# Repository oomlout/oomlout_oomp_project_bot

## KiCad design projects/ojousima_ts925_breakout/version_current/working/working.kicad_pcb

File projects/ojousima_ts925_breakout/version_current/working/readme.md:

# OOMP Project  
## TS925-breakout  by ojousima  
  
oomp key: oomp_projects_flat_ojousima_ts925_breakout  
(snippet of original readme)  

  full source readme at [readme_src.md](readme_src.md)  
  
source repo at: [https://github.com/ojousima/TS925-breakout](https://github.com/ojousima/TS925-breakout)  
## Board  

## Schematic  

[schematic pdf](working_schematic.pdf)  
## Images

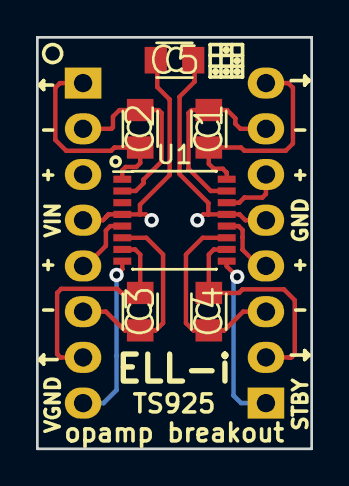
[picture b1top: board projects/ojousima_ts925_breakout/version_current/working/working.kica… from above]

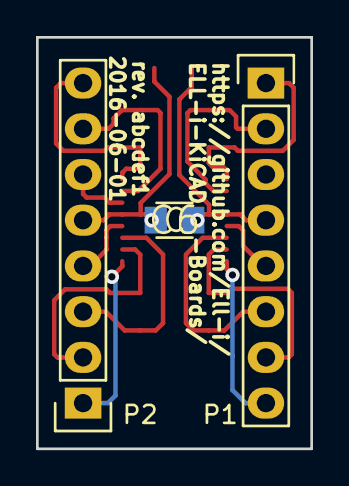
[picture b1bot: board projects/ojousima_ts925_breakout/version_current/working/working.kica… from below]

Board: 2 copper layers, 15.2 x 22.9 mm, 9 parts (3 on the bottom side), 15 nets.

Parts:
C1, C2, C3, C4, C5, C6: C; SMD0805-CAP-M
P1, P2: CONN_01X08; Pin_Header_Straight_1x08
U1: TS925; SSOP-16_4.4x5.2mm_Pitch0.65mm

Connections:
/1: C2.1, P1.1, U1.1
/2: C2.2, P1.2, U1.2
/5: P1.5, U1.5
/6: C3.2, P1.6, U1.6
/7: C3.1, P1.7, U1.7
/8: P1.8, U1.8
/9: P2.1, U1.9
/10: C4.1, P2.2, U1.10
/11: C4.2, P2.3, U1.11
/12: P2.4, U1.12
/14: P2.6, U1.14
/15: C1.2, P2.7, U1.15
/16: C1.1, P2.8, U1.16
GND: C5.2, C6.2, P2.5, U1.13
VCC: C5.1, C6.1, P1.4, U1.4

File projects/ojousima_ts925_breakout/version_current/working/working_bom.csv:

"Id";"Designator";"Footprint";"Quantity";"Designation";"Supplier and ref";
1;"C1,C2,C3,C4,C5,C6";"SMD0805-CAP-M";6;"C";;;
2;"P1,P2";"Pin_Header_Straight_1x08";2;"CONN_01X08";;;
3;"U1";"SSOP-16_4.4x5.2mm_Pitch0.65mm";1;"TS925";;;

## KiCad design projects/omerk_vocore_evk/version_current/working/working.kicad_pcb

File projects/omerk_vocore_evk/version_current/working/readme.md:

# OOMP Project  
## vocore-evk  by omerk  
  
oomp key: oomp_projects_flat_omerk_vocore_evk  
(snippet of original readme)  
  
- vocore-evk  
  
An evaluation kit for [VoCore](https://www.indiegogo.com/projects/vocore-a-coin-sized-linux-computer-with-wifi), the coin-sized Linux computer with WiFi.  

--- Design Status  
  
Alpha (untested!)  
  
--- License  

This work is licensed under a [Creative Commons Attribution-ShareAlike 4.0 International License](http://creativecommons.org/licenses/by-sa/4.0/).  
  
  full source readme at [readme_src.md](readme_src.md)  
  
source repo at: [https://github.com/omerk/vocore-evk](https://github.com/omerk/vocore-evk)  
## Board  

## Schematic  

[schematic pdf](working_schematic.pdf)  
## Images

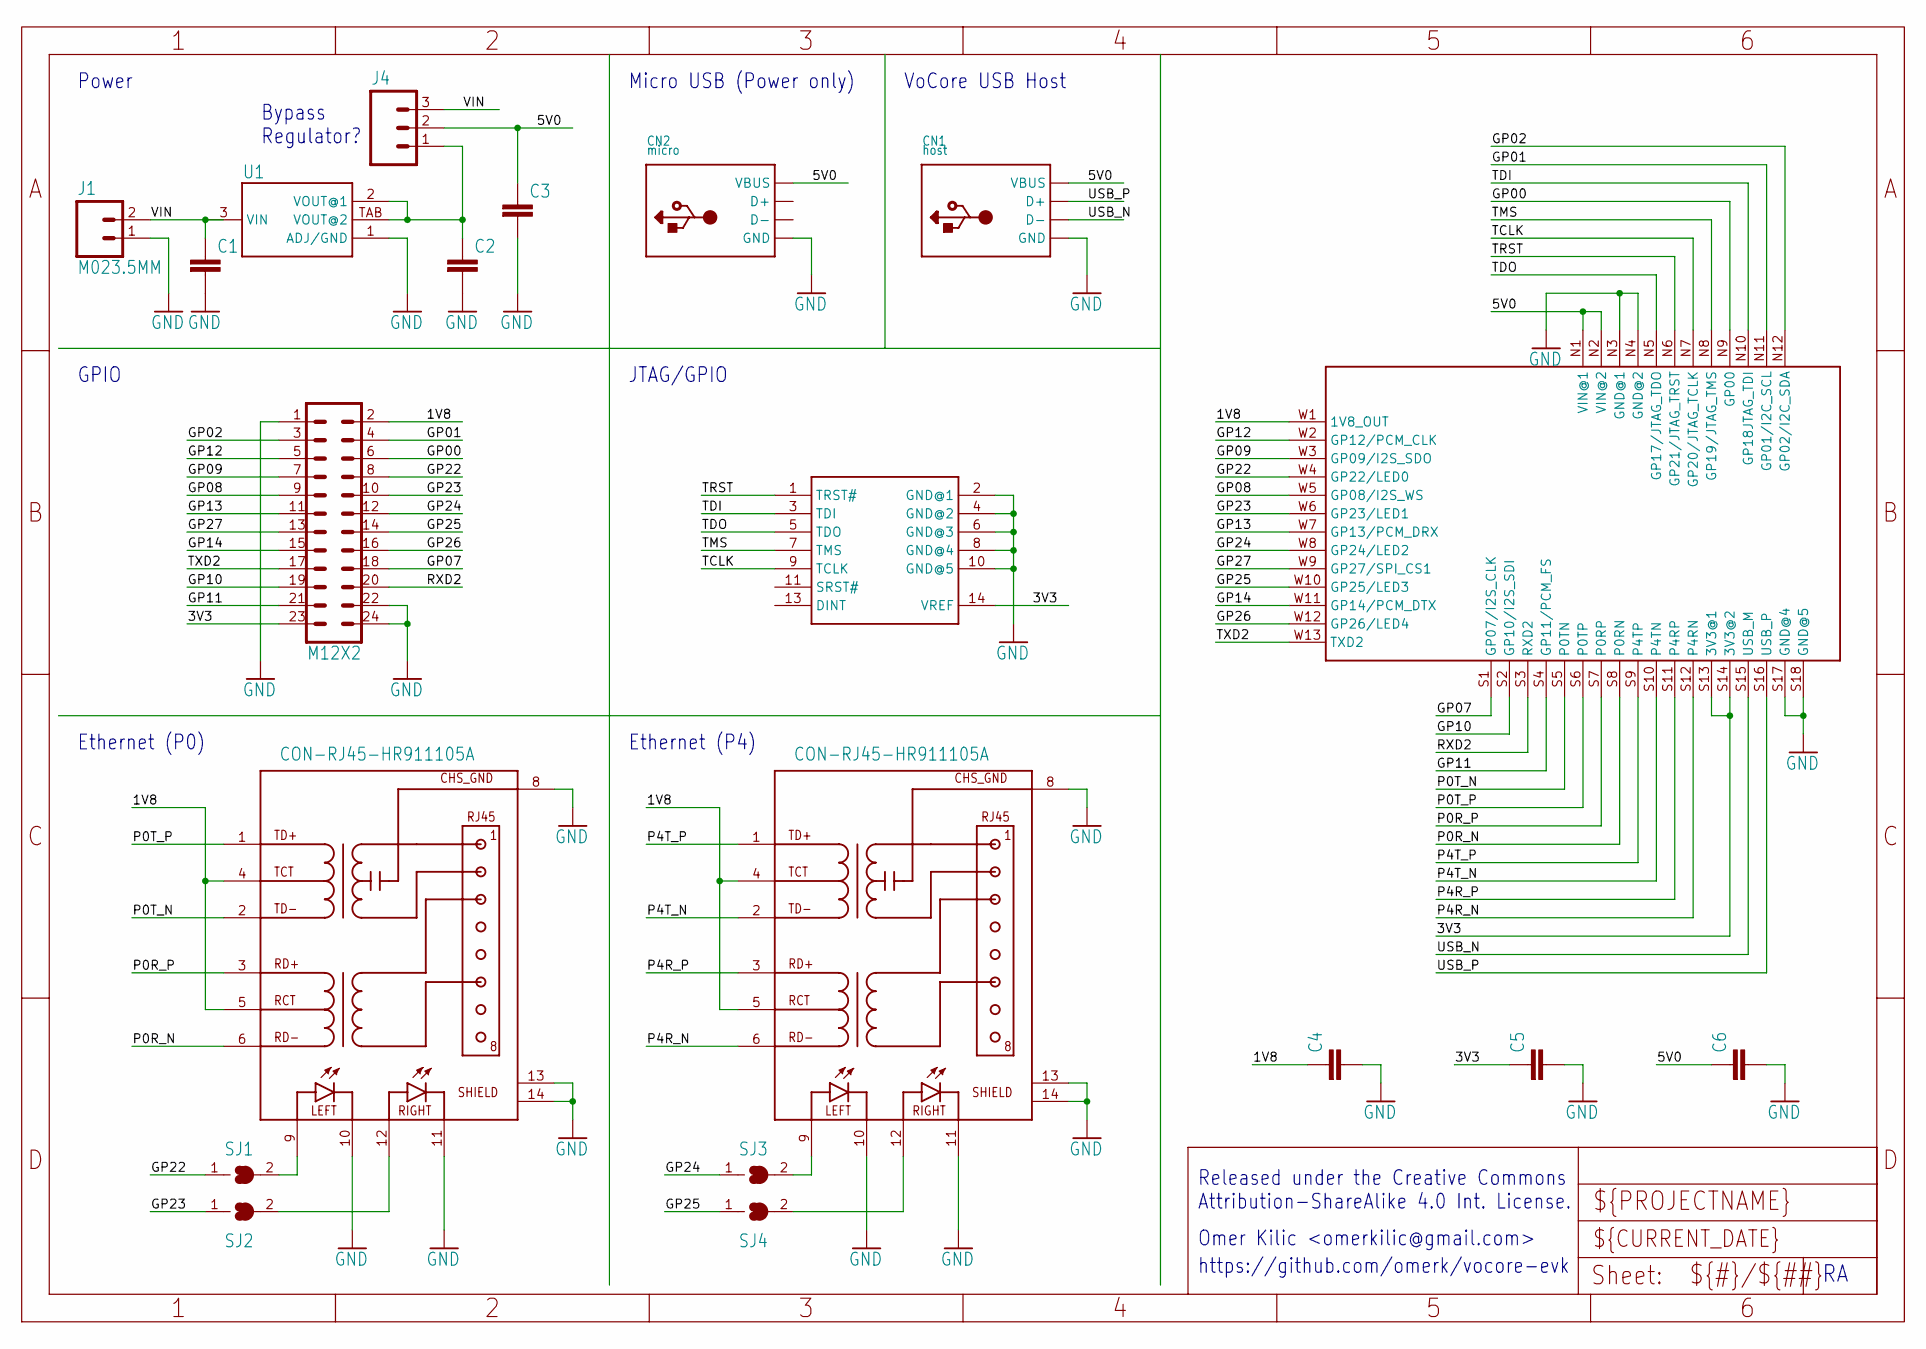
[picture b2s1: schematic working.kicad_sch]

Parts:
C1, C2, C3, C4, C5, C6: C-EUC0805; C0805
CN1: host; USB-A-FEMALE-TH
CN2: micro; USB-MOLEX-47346-0001
CN3, CN4: CON-RJ45-HR911105A; HR911105A
J1: M023.5MM; SCREWTERMINAL-3.5MM-2
J2: EJTAG_MIPS; M2X7
J3: M12X2; M2X12
J4: M03PTH; 1X03
MOD1: VOCORE_V10A
SJ1, SJ2, SJ3, SJ4: SJ
U1: LDO1117-SOT223; SOT223-3L

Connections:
1V8: C4.1, CN3.4 (TCT), CN3.5 (RCT), CN4.4 (TCT), CN4.5 (RCT), J3.2, MOD1.W1 (1V8_OUT)
3V3: C5.1, J2.14 (VREF), J3.23, MOD1.S13 (3V3@1), MOD1.S14 (3V3@2)
5V0: C3.1, C6.1, CN1.VBUS, CN2.VBUS, J4.2, MOD1.N1 (VIN@1), MOD1.N2 (VIN@2)
GND: C1.2, C2.2, C3.2, C4.2, C5.2, C6.2, CN1.GND, CN2.GND, CN3.8 (CHS_GND), CN3.10 (LEFT_GRN_LED_K), CN3.11 (RIGHT_YLW_LED_K), CN3.13 (SHIELD@1), CN3.14 (SHIELD@2), CN4.8 (CHS_GND), CN4.10 (LEFT_GRN_LED_K), CN4.11 (RIGHT_YLW_LED_K), CN4.13 (SHIELD@1), CN4.14 (SHIELD@2), J1.1, J2.2 (GND@1), J2.4 (GND@2), J2.6 (GND@3), J2.8 (GND@4), J2.10 (GND@5), J3.1, J3.22, J3.24, MOD1.N3 (GND@1), MOD1.N4 (GND@2), MOD1.S17 (GND@4), MOD1.S18 (GND@5), U1.1 (ADJ/GND)
GP00: J3.6, MOD1.N9 (GP00)
GP01: J3.4, MOD1.N11 (GP01/I2C_SCL)
GP02: J3.3, MOD1.N12 (GP02/I2C_SDA)
GP07: J3.18, MOD1.S1 (GP07/I2S_CLK)
GP08: J3.9, MOD1.W5 (GP08/I2S_WS)
GP09: J3.7, MOD1.W3 (GP09/I2S_SDO)
GP10: J3.19, MOD1.S2 (GP10/I2S_SDI)
GP11: J3.21, MOD1.S4 (GP11/PCM_FS)
GP12: J3.5, MOD1.W2 (GP12/PCM_CLK)
GP13: J3.11, MOD1.W7 (GP13/PCM_DRX)
GP14: J3.15, MOD1.W11 (GP14/PCM_DTX)
GP22: J3.8, MOD1.W4 (GP22/LED0), SJ1.1
GP23: J3.10, MOD1.W6 (GP23/LED1), SJ2.1
GP24: J3.12, MOD1.W8 (GP24/LED2), SJ3.1
GP25: J3.14, MOD1.W10 (GP25/LED3), SJ4.1
GP26: J3.16, MOD1.W12 (GP26/LED4)
GP27: J3.13, MOD1.W9 (GP27/SPI_CS1)
LED1: CN3.12 (RIGHT_YLW_LED_A), SJ2.2
unnamed: CN3.9 (LEFT_GRN_LED_A), SJ1.2
unnamed: CN4.9 (LEFT_GRN_LED_A), SJ3.2
unnamed: CN4.12 (RIGHT_YLW_LED_A), SJ4.2
P0R_N: CN3.6 (RD-), MOD1.S8 (P0RN)
P0R_P: CN3.3 (RD+), MOD1.S7 (P0RP)
P0T_N: CN3.2 (TD-), MOD1.S5 (P0TN)
P0T_P: CN3.1 (TD+), MOD1.S6 (P0TP)
P4R_N: CN4.6 (RD-), MOD1.S12 (P4RN)
P4R_P: CN4.3 (RD+), MOD1.S11 (P4RP)
P4T_N: CN4.2 (TD-), MOD1.S10 (P4TN)
P4T_P: CN4.1 (TD+), MOD1.S9 (P4TP)
RXD2: J3.20, MOD1.S3 (RXD2)
TCLK: J2.9 (TCLK), MOD1.N7 (GP20/JTAG_TCLK)
TDI: J2.3 (TDI), MOD1.N10 (GP18JTAG_TDI)
TDO: J2.5 (TDO), MOD1.N5 (GP17/JTAG_TDO)
TMS: J2.7 (TMS), MOD1.N8 (GP19/JTAG_TMS)
TRST: J2.1 (TRST#), MOD1.N6 (GP21/JTAG_TRST)
TXD2: J3.17, MOD1.W13 (TXD2)
USB_N: CN1.D-, MOD1.S15 (USB_M)
USB_P: CN1.D+, MOD1.S16 (USB_P)
VIN: C1.1, J1.2, J4.3, U1.3 (VIN)
VREG: C2.1, J4.1, U1.2 (VOUT@1), U1.TAB (VOUT@2)

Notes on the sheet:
Power
Ethernet (P4)
Omer Kilic <omerkilic@gmail.com>
Released under the Creative Commons Attribution-ShareAlike 4.0 Int. License.
Ethernet (P0)
Bypass Regulator?
GPIO
VoCore USB Host
JTAG/GPIO
Micro USB (Power only)
https://github.com/omerk/vocore-evk

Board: 2 copper layers, 24 parts (0 on the bottom side), 44 nets, no tracks yet.

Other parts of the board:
@HOLE0, @HOLE1, @HOLE2, @HOLE3: (no value)

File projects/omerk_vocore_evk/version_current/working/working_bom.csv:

"Id";"Designator";"Footprint";"Quantity";"Designation";"Supplier and ref";
1;"@HOLE0,@HOLE3,@HOLE1,@HOLE2";"";4;"";;;
2;"SJ2,SJ3,SJ4,SJ1";"SJ";4;"";;;
3;"U1";"SOT223-3L";1;"";;;
4;"J3";"M2X12";1;"M12X2";;;
5;"CN3,CN4";"HR911105A";2;"CON-RJ45-HR911105A";;;
6;"C1,C5,C2,C3,C4,C6";"C0805";6;"";;;
7;"J1";"SCREWTERMINAL-3.5MM-2";1;"M023.5MM";;;
8;"CN1";"USB-A-FEMALE-TH";1;"host";;;
9;"CN2";"USB-MOLEX-47346-0001";1;"micro";;;
10;"MOD1";"VOCORE_V10A";1;"VOCORE_V10A";;;
11;"J2";"M2X7";1;"EJTAG_MIPS";;;
12;"J4";"1X03";1;"";;;

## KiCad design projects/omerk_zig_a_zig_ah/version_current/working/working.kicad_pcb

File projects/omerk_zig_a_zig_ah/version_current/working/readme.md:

# zig-a-zig-ah by omerk  
This is a harvested standardized copy of a project from github.  
The original project can be found at:  
https://github.com/omerk/zig-a-zig-ah  
Please consult that link for additional, details, files, and license information.  
Note: It was auto harvested and if the original repo had more than one board file or anything out of the ordinary the files here are likely not representative.

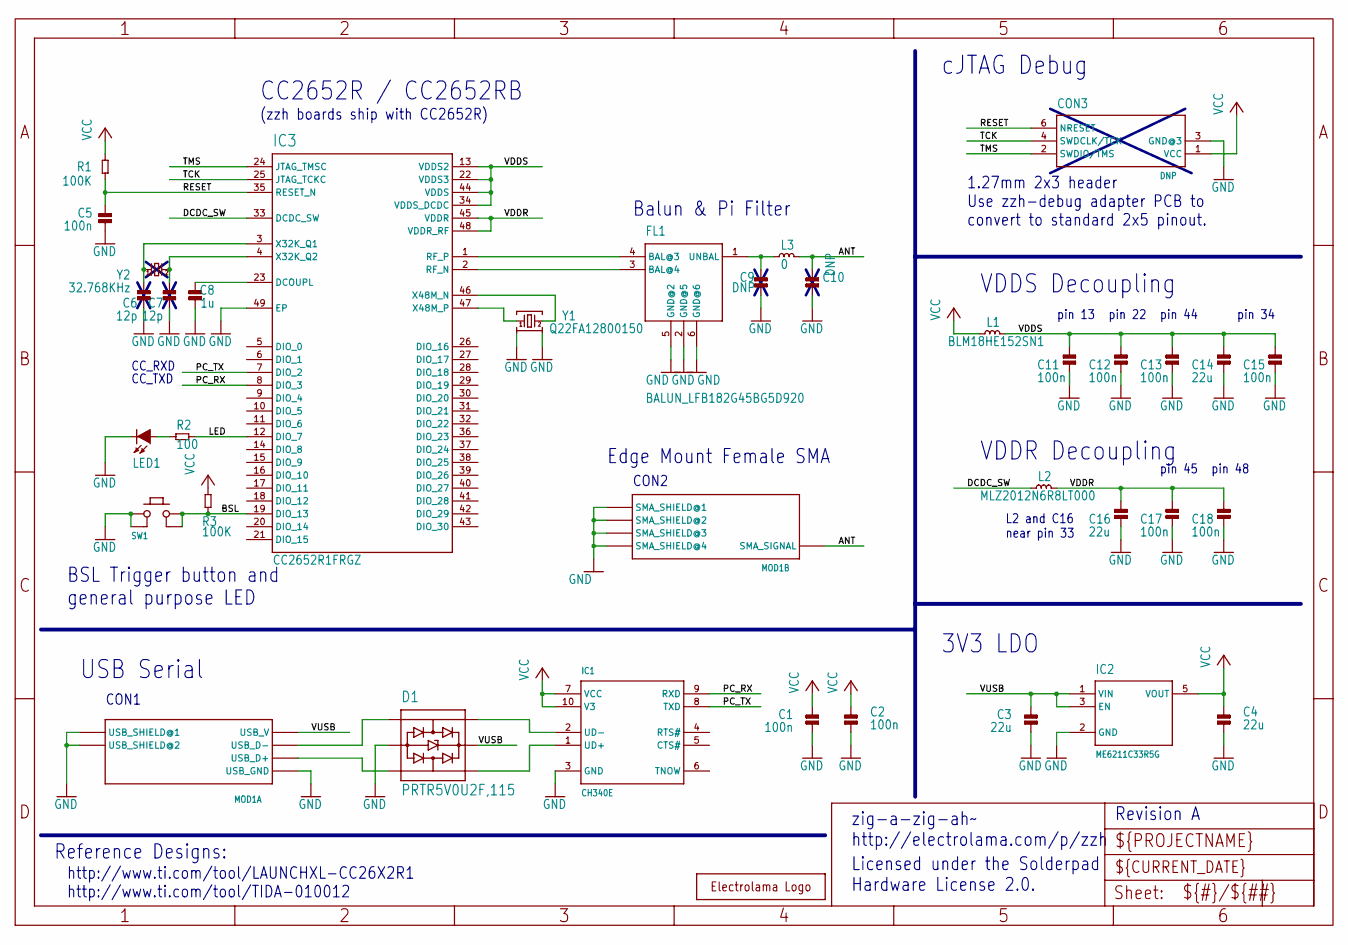
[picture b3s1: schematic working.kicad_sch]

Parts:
C1, C2, C5, C11, C12, C13, C15, C17, C18: 100n; _PKG_C_0402
C3, C4, C14, C16: 22u; _PKG_C_0805
C6, C7: 12p; _PKG_C_0402
C8: 1u; _PKG_C_0402
C9, C10: DNP; _PKG_C_0402
CON3: DNP; DEBUG_CORTEX_5PIN
D1: PRTR5V0U2F,115; _PKG_SOT886_JEDEC-MO-252
FL1: BALUN_LFB182G45BG5D920; LFB182G45BG5D920
IC1: CH340E; _PKG_MSOP10_TI-DGS10
IC2: ME6211C33R5G; SOT65P212X110-5N
IC3: CC2652R1FRGZ; QFN50P700X700X100-49N
L1: BLM18HE152SN1; _PKG_L_0603
L2: MLZ2012N6R8LT000; _PKG_C_0805
L3: 0; _PKG_L_0402
LED1: LED-0603; _PKG_LED_0603
MOD1: ZZH_MODULE
R1, R3: 100K; _PKG_C_0402
R2: 100; _PKG_C_0402
SW1: K2-1177SW-D4DW-06
U$5: LOGO-ELECTROLAMA; ELECTROLAMA
Y1: Q22FA12800150; XTAL-4P-2016
Y2: 32.768KHz; XTAL-2P-3215

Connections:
ANT: C10.2, L3.2, MOD1.SMA_SIGNAL
BSL: IC3.19 (DIO_13), R3.2, SW1.3 (2_1), SW1.4 (2_2)
DCDC_SW: IC3.33 (DCDC_SW), L2.1
DCOUPL: C8.2, IC3.23 (DCOUPL)
GND: C1.1, C2.1, C3.2, C4.2, C5.1, C6.1, C7.1, C8.1, C9.1, C10.1, C11.2, C12.2, C13.2, C14.2, C15.2, C16.2, C17.2, C18.2, CON3.3 (GND@3), D1.2, FL1.2 (GND@5), FL1.5 (GND@2), FL1.6 (GND@6), IC1.3 (GND), IC2.2 (GND), IC3.49 (EP), LED1.C, MOD1.SMA_SHIELD_1 (SMA_SHIELD@1), MOD1.SMA_SHIELD_2 (SMA_SHIELD@2), MOD1.SMA_SHIELD_3 (SMA_SHIELD@3), MOD1.SMA_SHIELD_4 (SMA_SHIELD@4), MOD1.USB_GND, MOD1.USB_SHIELD_1 (USB_SHIELD@1), MOD1.USB_SHIELD_2 (USB_SHIELD@2), SW1.1 (1_1), SW1.2 (1_2), Y1.2, Y1.4
LED: IC3.12 (DIO_7), R2.1
unnamed: LED1.A, R2.2
PC_RX: IC1.9 (RXD), IC3.8 (DIO_3)
PC_TX: IC1.8 (TXD), IC3.7 (DIO_2)
RESET: C5.2, CON3.6 (NRESET), IC3.35 (RESET_N), R1.1
RF_N: FL1.3 (BAL@4), IC3.2 (RF_N)
RF_P: FL1.4 (BAL@3), IC3.1 (RF_P)
TCK: CON3.4 (SWDCLK/TCK), IC3.25 (JTAG_TCKC)
TMS: CON3.2 (SWDIO/TMS), IC3.24 (JTAG_TMSC)
UD+: D1.6, IC1.1 (UD+)
UD-: D1.4, IC1.2 (UD-)
UNBAL: C9.2, FL1.1 (UNBAL), L3.1
USB_D+: D1.1, MOD1.USB_D+
USB_D-: D1.3, MOD1.USB_D-
VCC: C1.2, C2.2, C4.1, CON3.1 (VCC), IC1.7 (VCC), IC1.10 (V3), IC2.5 (VOUT), L1.1, R1.2, R3.1
VDDR: C16.1, C17.1, C18.1, IC3.45 (VDDR), IC3.48 (VDDR_RF), L2.2
VDDS: C11.1, C12.1, C13.1, C14.1, C15.1, IC3.13 (VDDS2), IC3.22 (VDDS3), IC3.34 (VDDS_DCDC), IC3.44 (VDDS), L1.2
VUSB: C3.1, D1.5, IC2.1 (VIN), IC2.3 (EN), MOD1.USB_V
X32K_Q1: C6.2, IC3.3 (X32K_Q1), Y2.1
X32K_Q2: C7.2, IC3.4 (X32K_Q2), Y2.2
X48M_N: IC3.46 (X48M_N), Y1.3
X48M_P: IC3.47 (X48M_P), Y1.1

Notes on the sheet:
VDDS Decoupling
CC2652R / CC2652RB
cJTAG Debug
pin 44
zig-a-zig-ah~ http://electrolama.com/p/zzh
BSL Trigger button and general purpose LED
Revision A
CON1
Edge Mount Female SMA
1.27mm 2x3 header Use zzh-debug adapter PCB to convert to standard 2x5 pinout.
CC_RXD
http://www.ti.com/tool/LAUNCHXL-CC26X2R1 http://www.ti.com/tool/TIDA-010012
pin 45
pin 34
pin 13
pin 48
3V3 LDO
Reference Designs:
L2 and C16 near pin 33
USB Serial
(zzh boards ship with CC2652R)
Licensed under the Solderpad Hardware License 2.0.
CON2
pin 22
Balun & Pi Filter
VDDR Decoupling
CC_TXD

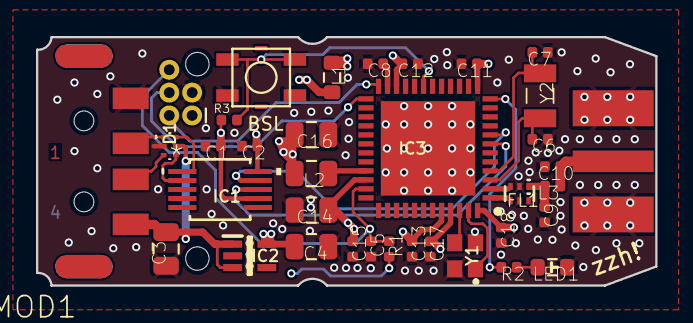
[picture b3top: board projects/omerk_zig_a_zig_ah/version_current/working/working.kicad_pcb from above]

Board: 4 copper layers, 34.4 x 13.8 mm, 36 parts (1 on the bottom side), 27 nets.

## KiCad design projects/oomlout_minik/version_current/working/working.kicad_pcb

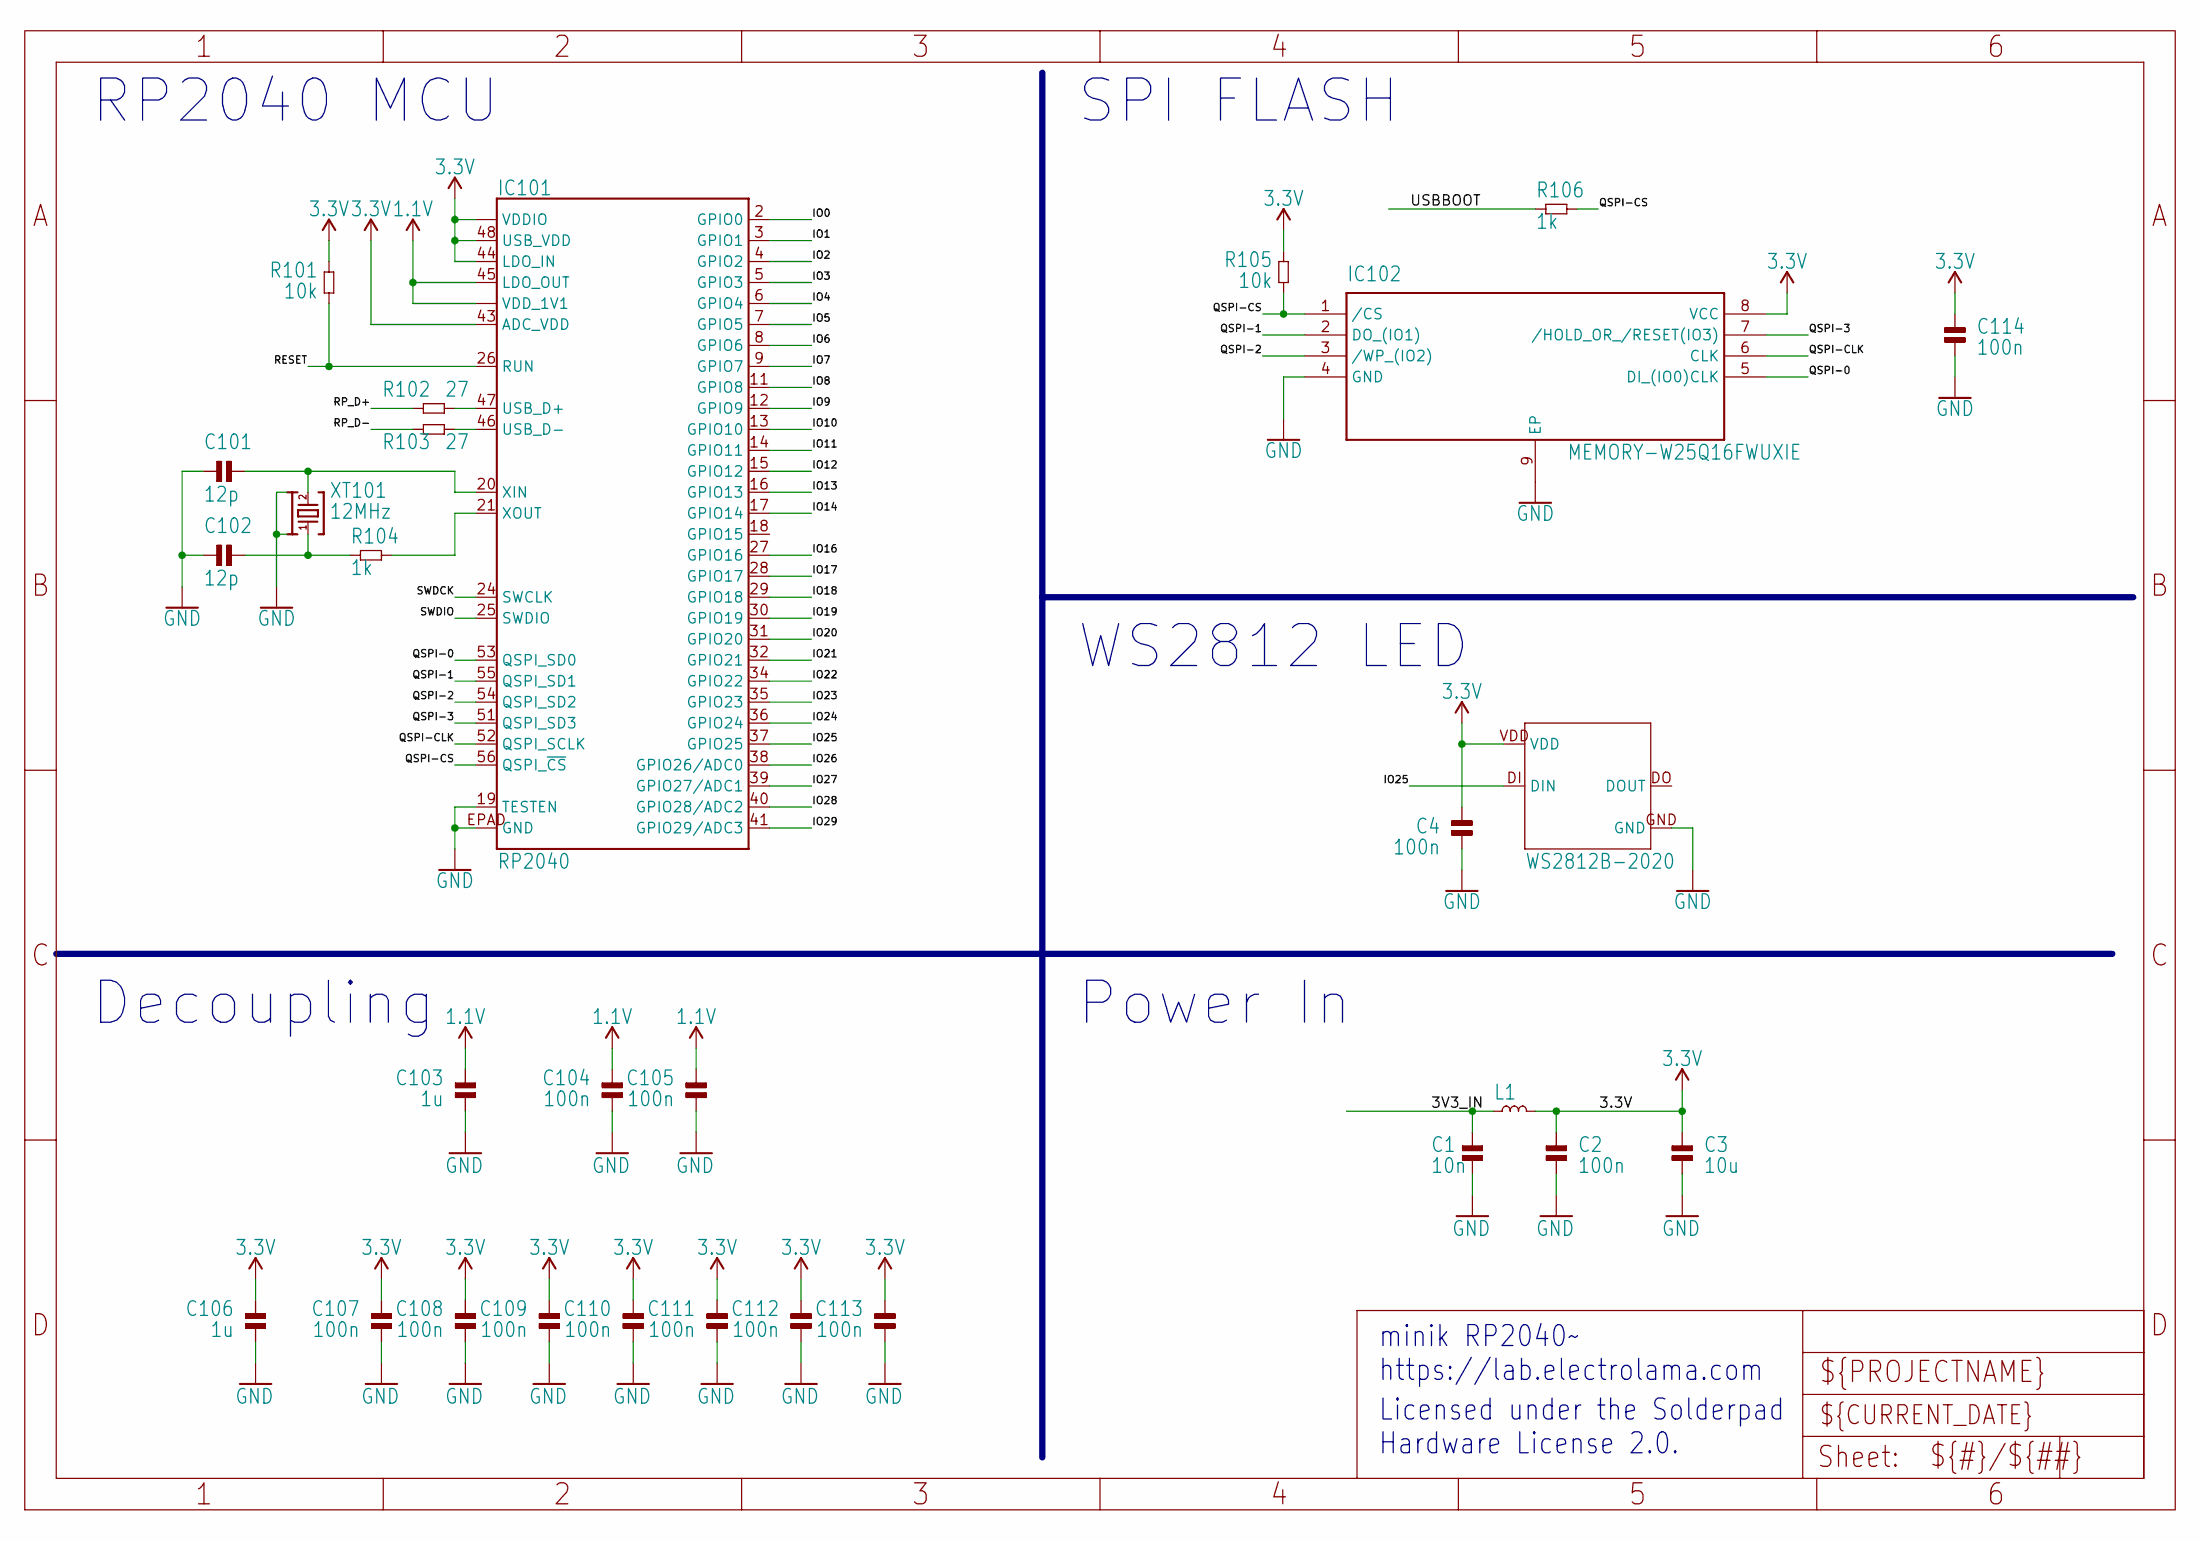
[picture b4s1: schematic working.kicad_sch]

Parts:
C1: 10n; _PKG_C_0402
C2, C4, C104, C105, C107, C108, C109, C110, C111, C112, C113, C114: 100n; _PKG_C_0402
C3: 10u; _PKG_C_0402
C101, C102: 12p; _PKG_C_0402
C103, C106: 1u; _PKG_C_0402
IC101: RP2040; QFN-56
IC102: MEMORY-W25Q16FWUXIE; SON50P300X200X60-9N
L1: INDUCTOR-0402; _PKG_L_0402
LED1: WS2812B-2020
R101, R105: 10k; _PKG_R_0402
R102, R103: 27; _PKG_R_0402
R104, R106: 1k; _PKG_R_0402
XT101: 12MHz; XTAL-4P-3225

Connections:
1.1V: C103.2, C104.2, C105.2, IC101.23 (VDD_1V1), IC101.45 (LDO_OUT), IC101.50 (VDD_1V1)
3.3V: C2.2, C3.2, C4.2, C106.2, C107.2, C108.2, C109.2, C110.2, C111.2, C112.2, C113.2, C114.2, IC101.1 (VDDIO), IC101.10 (VDDIO), IC101.22 (VDDIO), IC101.33 (VDDIO), IC101.42 (VDDIO), IC101.43 (ADC_VDD), IC101.44 (LDO_IN), IC101.48 (USB_VDD), IC101.49 (VDDIO), IC102.8 (VCC), L1.2, LED1.VDD, R101.2, R105.2
3V3_IN: C1.2, L1.1
GND: C1.1, C2.1, C3.1, C4.1, C101.1, C102.1, C103.1, C104.1, C105.1, C106.1, C107.1, C108.1, C109.1, C110.1, C111.1, C112.1, C113.1, C114.1, IC101.19 (TESTEN), IC101.EPAD (GND), IC102.4 (GND), IC102.9 (EP), LED1.GND, XT101.2, XT101.4
IO0: IC101.2 (GPIO0)
IO1: IC101.3 (GPIO1)
IO2: IC101.4 (GPIO2)
IO3: IC101.5 (GPIO3)
IO4: IC101.6 (GPIO4)
IO5: IC101.7 (GPIO5)
IO6: IC101.8 (GPIO6)
IO7: IC101.9 (GPIO7)
IO8: IC101.11 (GPIO8)
IO9: IC101.12 (GPIO9)
IO10: IC101.13 (GPIO10)
IO11: IC101.14 (GPIO11)
IO12: IC101.15 (GPIO12)
IO13: IC101.16 (GPIO13)
IO14: IC101.17 (GPIO14)
IO16: IC101.27 (GPIO16)
IO17: IC101.28 (GPIO17)
IO18: IC101.29 (GPIO18)
IO19: IC101.30 (GPIO19)
IO20: IC101.31 (GPIO20)
IO21: IC101.32 (GPIO21)
IO22: IC101.34 (GPIO22)
IO23: IC101.35 (GPIO23)
IO24: IC101.36 (GPIO24)
IO25: IC101.37 (GPIO25), LED1.DI (DIN)
IO26: IC101.38 (GPIO26/ADC0)
IO27: IC101.39 (GPIO27/ADC1)
IO28: IC101.40 (GPIO28/ADC2)
IO29: IC101.41 (GPIO29/ADC3)
unnamed: IC101.47 (USB_D+), R102.2
unnamed: IC101.46 (USB_D-), R103.2
QSPI-0: IC101.53 (QSPI_SD0), IC102.5 (DI_(IO0)CLK)
QSPI-1: IC101.55 (QSPI_SD1), IC102.2 (DO_(IO1))
QSPI-2: IC101.54 (QSPI_SD2), IC102.3 (/WP_(IO2))
QSPI-3: IC101.51 (QSPI_SD3), IC102.7 (/HOLD_OR_/RESET(IO3))
QSPI-CLK: IC101.52 (QSPI_SCLK), IC102.6 (CLK)
QSPI-CS: IC101.56 (QSPI_~CS), IC102.1 (/CS), R105.1, R106.1
RESET: IC101.26 (RUN), R101.1
RP_D+: R102.1
RP_D-: R103.1
SWDCK: IC101.24 (SWCLK)
SWDIO: IC101.25 (SWDIO)
USBBOOT: R106.2
X1A: IC101.21 (XOUT), R104.2
X1B: C102.2, R104.1, XT101.1
X2: C101.2, IC101.20 (XIN), XT101.3

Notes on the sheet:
Decoupling
WS2812 LED
Licensed under the Solderpad Hardware License 2.0.
minik RP2040~ https://lab.electrolama.com
RP2040 MCU
Power In
SPI FLASH

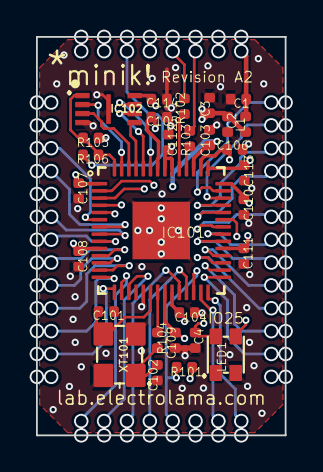
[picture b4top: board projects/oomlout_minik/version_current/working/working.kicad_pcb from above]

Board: 4 copper layers, 13.8 x 22.1 mm, 29 parts (0 on the bottom side), 17 nets.

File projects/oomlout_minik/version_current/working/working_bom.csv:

"Id";"Designator";"Footprint";"Quantity";"Designation";"Supplier and ref";
1;"C108,C107,C105,C4,C113,C2,C112,C110,C104,C109,C111,C114";"_PKG_C_0402";12;"100n";;;
2;"C102,C101";"_PKG_C_0402";2;"12p";;;
3;"XT101";"XTAL-4P-3225";1;"12MHz";;;
4;"R106,R104";"_PKG_R_0402";2;"1k";;;
5;"LED1";"WS2812B-2020";1;"WS2812B-2020";;;
6;"R105,R101";"_PKG_R_0402";2;"10k";;;
7;"C103,C106";"_PKG_C_0402";2;"1u";;;
8;"C3";"_PKG_C_0402";1;"10u";;;
9;"R102,R103";"_PKG_R_0402";2;"27";;;
10;"IC102";"SON50P300X200X60-9N";1;"MEMORY-W25Q16FWUXIE";;;
11;"C1";"_PKG_C_0402";1;"10n";;;
12;"L1";"_PKG_L_0402";1;"";;;
13;"IC101";"QFN-56";1;"RP2040";;;

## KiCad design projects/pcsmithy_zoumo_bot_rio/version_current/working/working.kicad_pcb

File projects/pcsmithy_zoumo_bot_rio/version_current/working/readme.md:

# OOMP Project  
## Zoumo-Bot-Rio  by PCSmithy  
  
oomp key: oomp_projects_flat_pcsmithy_zoumo_bot_rio  
(snippet of original readme)  
  
- Zoumo-Bot-Rio  
An Atmega32u4 and a set up motor drivers heavily modeled off the Sparkfun Arduino Pro Micro and the Adafruit Motor Driver Shield v2  
  
https://www.sparkfun.com/products/12640  
  
https://www.adafruit.com/product/1438  

  full source readme at [readme_src.md](readme_src.md)  
  
source repo at: [https://github.com/PCSmithy/Zoumo-Bot-Rio](https://github.com/PCSmithy/Zoumo-Bot-Rio)  
## Board  

## Schematic  

[schematic pdf](working_schematic.pdf)  
## Images

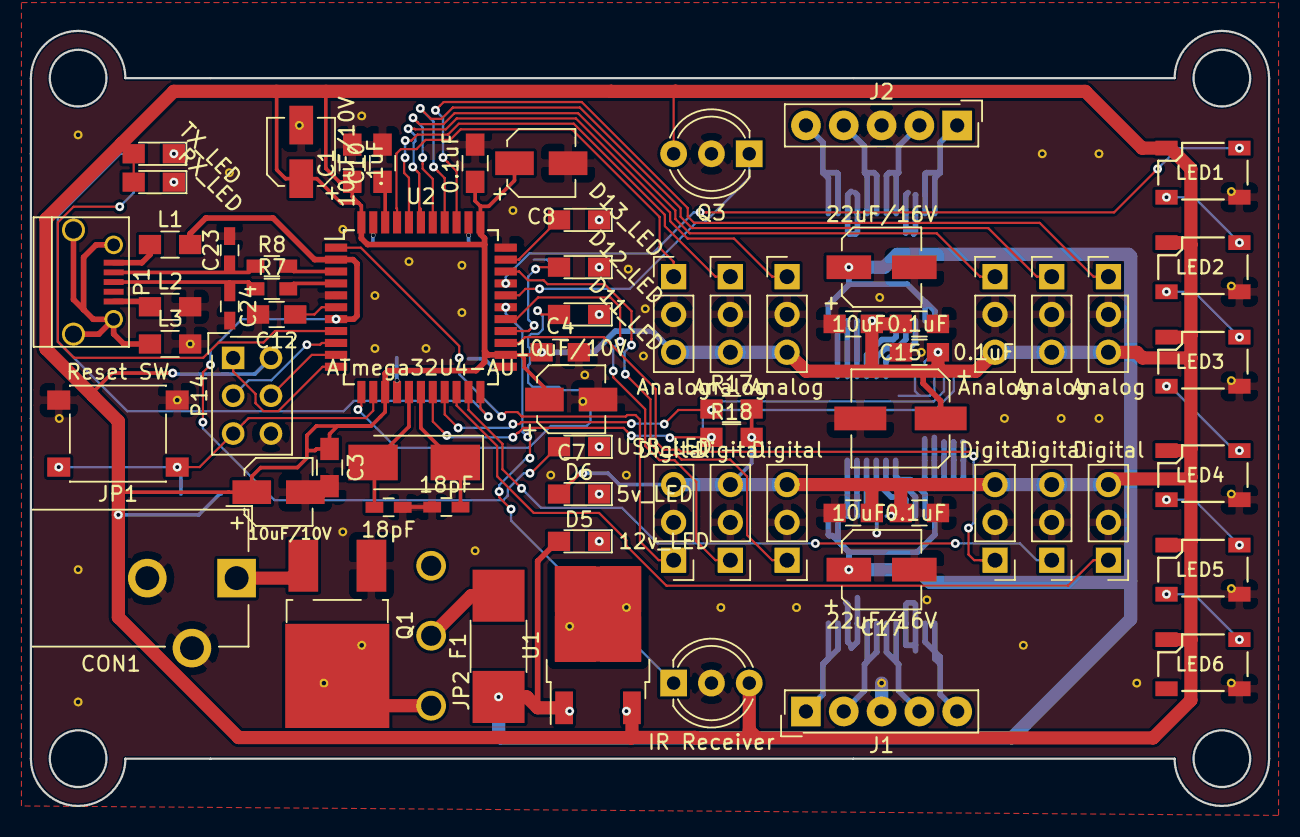
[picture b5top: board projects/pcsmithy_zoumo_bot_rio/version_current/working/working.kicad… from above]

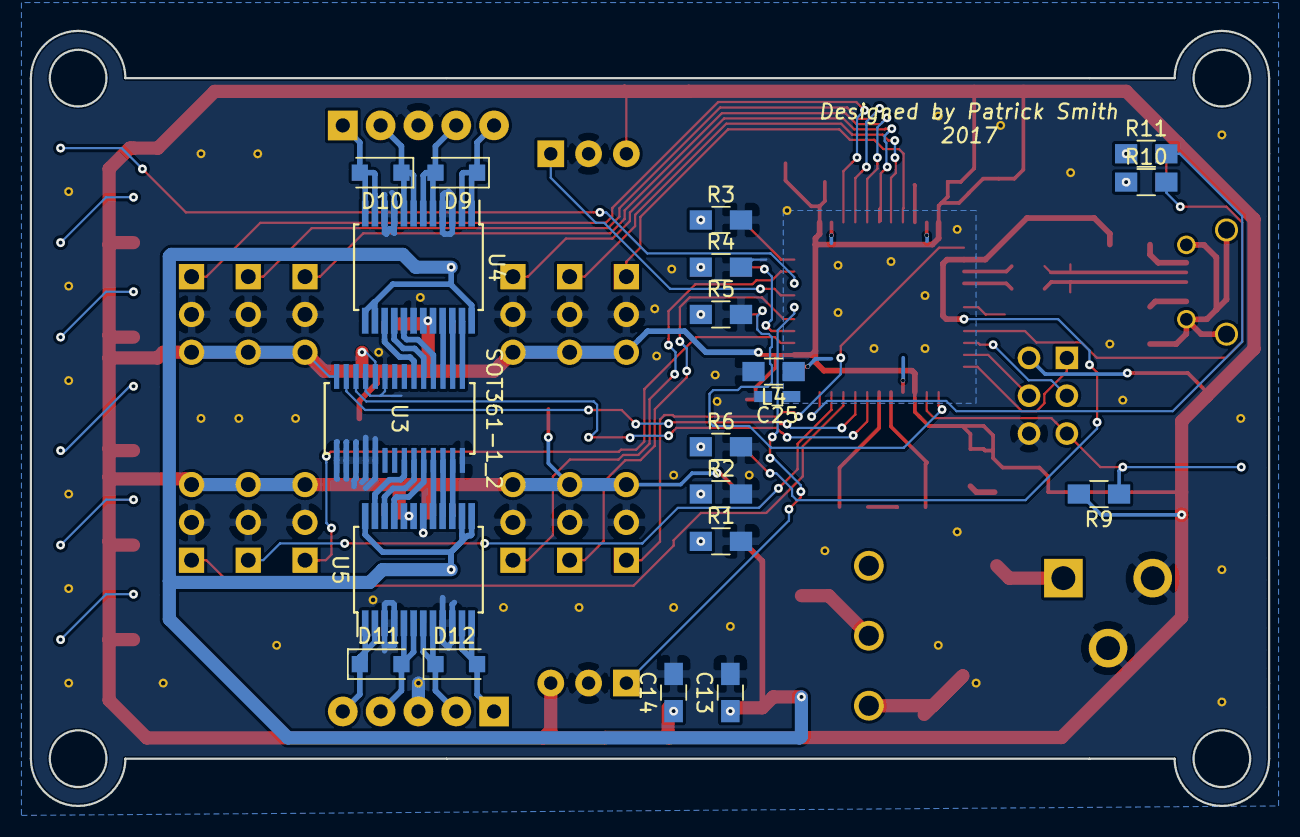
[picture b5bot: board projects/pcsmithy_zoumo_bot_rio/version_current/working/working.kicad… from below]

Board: 2 copper layers, 83.2 x 52.1 mm, 89 parts (20 on the bottom side), 76 nets.

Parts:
C1: .1uF; C_0805_HandSoldering
C2, C3, C4, C10, C14, C19, C20, C21: 0.1uF; C_0805_HandSoldering
C5, C6, C7, C8: 10uF/10V; CP_Elec_4x4.5
C9, C11: 18pF; C_0603_HandSoldering
C12: 1uF; C_0805_HandSoldering
C13: 0.33uF; C_0805_HandSoldering
C15: 100uF; CP_Elec_6.3x7.7
C16, C17: 22uF/16V; CP_Elec_5x5.8
C18, C22: 10uF; C_0805_HandSoldering
C23, C24, C25: C_Small; C_0603_HandSoldering
CON1: BARREL_JACK; Barrel_Jack_CUI_PJ-102AH
D1: 12v_LED; LED_0805_HandSoldering
D2: D13_LED; LED_0805_HandSoldering
D3: D12_LED; LED_0805_HandSoldering
D4: D11_LED; LED_0805_HandSoldering
D5: 5v_LED; LED_0805_HandSoldering
D6: USB_LED; LED_0805_HandSoldering
D7: RX_LED; LED_0805_HandSoldering
D8: TX_LED; LED_0805_HandSoldering
D9, D10, D11, D12: FlyBack; D_SOD-123F
F1: Polyfuse; R_1812_HandSoldering
J1, J2: Screw_Terminal_1x05; SL-105-X-XX_1x05
JP1: Reset SW; SW_SPST_PTS645
JP2: PWR SW; Slide SW
L1, L2, L3, L4: Ferrite_Bead_Small; R_0805_HandSoldering
LED1, LED2, LED3, LED4, LED5, LED6: NeoPixel; WS2812B_smallsilk
P1: USB_OTG; USB_Micro-B
P2, P4, P6, P8, P10, P12: Analog; Socket_Strip_Straight_1x03_Pitch2.54mm
P3, P5, P7, P9, P11, P13: Digital; Socket_Strip_Straight_1x03_Pitch2.54mm
P14: CONN_01X06; SDL-106-X-XX_2x03
Q1: Q_PMOS_GDS; TO-252-2_Rectifier
Q2, Q3: IR Receiver; LED_D5.0mm-3
R1: 500; R_0805_HandSoldering
R2, R3, R4, R5, R6: 150; R_0805_HandSoldering
R7, R8: 22; R_0603_HandSoldering
R9: 10K; R_0805_HandSoldering
R10, R11: 330; R_0805_HandSoldering
R17, R18: 10k; R_0805_HandSoldering
U1: ZLDO1117K50TC; TO-252-2
U2: ATmega32U4-AU; TQFP-44_10x10mm_Pitch0.8mm
U3: SOT361-1_2; PCA9685PW
U4, U5: TB6612FNG; SSOP-24_5.3x8.2mm_Pitch0.65mm
Y1: 16MHz; Crystal_SMD_Abracon_ABM3-2pin_5.0x3.2mm_HandSoldering

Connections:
+5V: C1.1, C2.1, C3.1, C4.1, C5.1, C6.1, C7.1, C8.1, C14.1, C15.1, C18.1, C19.1, C20.1, C21.1, C22.1, D5.2, D7.2, D8.2, LED1.3, LED2.3, LED3.3, LED4.3, LED5.3, LED6.3, P2.3, P3.3, P4.3, P5.3, P6.3, P7.3, P8.3, P9.3, P10.3, P11.3, P12.3, P13.3, P14.2, Q2.3, Q3.3, R9.2, R17.2, R18.2, U1.3, U2.14, U2.24, U2.34, U2.44, U3.24, U3.28, U4.19, U4.20, U5.19, U5.20
+12V: C13.1, C16.1, C17.1, D1.2, F1.1, U1.1, U4.13, U4.14, U4.24, U5.13, U5.14, U5.24
/AREF: C10.1, U2.42
/MotorDriver/A01: D9.1, J2.5, U4.1, U4.2
/MotorDriver/A02: D9.2, J2.4, U4.5, U4.6
/MotorDriver/B01: D10.1, J2.2, U4.7, U4.8
/MotorDriver/B02: D10.2, J2.1, U4.11, U4.12
/MotorDriver/C01: D11.1, J1.5, U5.1, U5.2
/MotorDriver/C02: D11.2, J1.4, U5.5, U5.6
/MotorDriver/D01: D12.1, J1.2, U5.7, U5.8
/MotorDriver/D02: D12.2, J1.1, U5.11, U5.12
/MotorDriver/PWM2: U3.8, U5.23
/MotorDriver/PWM3: U3.9, U5.22
/MotorDriver/PWM4: U3.10, U5.21
/MotorDriver/PWM5: U3.11, U5.17
/MotorDriver/PWM6: U3.12, U5.16
/MotorDriver/PWM7: U3.13, U5.15
/MotorDriver/PWM8: U3.15, U4.23
/MotorDriver/PWM9: U3.16, U4.22
/MotorDriver/PWM10: U3.17, U4.21
/MotorDriver/PWM11: U3.18, U4.17
/MotorDriver/PWM12: U3.19, U4.16
/MotorDriver/PWM13: U3.20, U4.15
/Reset: JP1.1, P14.5, R9.1, U2.13
/SCL/D3: R18.1, U2.18, U3.26
/SDA/D2: R17.1, U2.19, U3.27
/dGnd: C25.1, L4.1, U2.15, U2.23, U2.35, U2.43
A0: P12.1, U2.36
A1: P10.1, U2.37
A2: P8.1, U2.38
A3: P6.1, U2.39
A4: P4.1, U2.40
A5: P2.1, U2.41
D0/RXI: P13.1, U2.20
D1/TXO: P11.1, U2.21
D4: P9.1, U2.25
D5: P7.1, U2.31
D6: P5.1, U2.27
D7: P3.1, U2.1
D8: Q2.1, U2.28
D9: Q3.1, U2.29
D10: LED1.2, U2.30
D11: D4.2, U2.12
D12: D3.2, U2.26
D13: D2.2, U2.32
D+: C24.1, P1.3, R7.1, R7.2, U2.4
D-: C23.1, P1.2, R8.1, R8.2, U2.3
GND: C1.2, C2.2, C3.2, C4.2, C5.2, C6.2, C7.2, C8.2, C9.2, C10.2, C11.2, C12.2, C13.2, C14.2, C15.2, C16.2, C17.2, C18.2, C19.2, C20.2, C21.2, C22.2, C23.2, C24.2, C25.2, CON1.2, CON1.3, J1.3, J2.3, JP1.2, L2.2, L3.2, L4.2, LED1.1, LED2.1, LED3.1, LED4.1, LED5.1, LED6.1, P2.2, P3.2, P4.2, P5.2, P6.2, P7.2, P8.2, P9.2, P10.2, P11.2, P12.2, P13.2, P14.6, Q1.1, Q2.2, Q3.2, R1.2, R2.2, R3.2, R4.2, R5.2, R6.2, U1.2, U2.5, U2.33, U3.1, U3.2, U3.3, U3.4, U3.5, U3.14, U3.23, U3.25, U4.3, U4.4, U4.9, U4.10, U4.18, U5.3, U5.4, U5.9, U5.10, U5.18
MISO: P14.1, U2.11
MOSI: P14.4, U2.10
unnamed: C9.1, U2.17, Y1.1
unnamed: C11.1, U2.16, Y1.2
unnamed: C12.1, U2.6
unnamed: CON1.1, Q1.3
unnamed: D1.1, R1.1
unnamed: D2.1, R3.1
unnamed: D3.1, R4.1
unnamed: D4.1, R5.1
unnamed: D5.1, R2.1
unnamed: D6.1, R6.1
unnamed: D7.1, R10.1
unnamed: D8.1, R11.1
unnamed: F1.2, JP2.2
unnamed: JP2.1, Q1.2
unnamed: L1.1, P1.1
unnamed: L2.1, P1.5
unnamed: L3.1, P1.6
unnamed: LED1.4, LED2.2
unnamed: LED2.4, LED3.2
unnamed: LED3.4, LED4.2
unnamed: LED4.4, LED5.2
unnamed: LED5.4, LED6.2
unnamed: R10.2, U2.8
unnamed: R11.2, U2.22
SCK: P14.3, U2.9
UVcc: D6.2, L1.2, U2.2, U2.7

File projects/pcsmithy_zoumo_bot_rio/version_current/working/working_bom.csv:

"Id";"Designator";"Footprint";"Quantity";"Designation";"Supplier and ref";
1;"REF**,REF**,REF**,REF**,REF**,REF**,REF**,REF**,REF**,REF**,REF**,REF**,REF**,REF**,REF**,REF**,REF**,REF**,REF**,REF**,REF**,REF**,REF**,REF**,REF**,REF**,REF**,REF**,REF**,REF**,REF**,REF**,REF**,REF**,REF**,REF**,REF**,REF**,REF**,REF**,REF**,REF**,REF**,REF**,REF**,REF**,REF**,REF**,REF**";"VIA-.6mm";49;"VIA-.6mm";;;
2;"U2";"TQFP-44_10x10mm_Pitch0.8mm";1;"ATmega32U4-AU";;;
3;"LED6,LED1,LED2,LED3,LED4,LED5";"WS2812B_smallsilk";6;"NeoPixel";;;
4;"C1";"C_0805_HandSoldering";1;".1uF";;;
5;"C2,C3,C4,C10,C14,C19,C20,C21";"C_0805_HandSoldering";8;"0.1uF";;;
6;"C5,C6,C7,C8";"CP_Elec_4x4.5";4;"10uF/10V";;;
7;"C9,C11";"C_0603_HandSoldering";2;"18pF";;;
8;"C12";"C_0805_HandSoldering";1;"1uF";;;
9;"C13";"C_0805_HandSoldering";1;"0.33uF";;;
10;"C15";"CP_Elec_6.3x7.7";1;"100uF";;;
11;"C16,C17";"CP_Elec_5x5.8";2;"22uF/16V";;;
12;"C18,C22";"C_0805_HandSoldering";2;"10uF";;;
13;"CON1";"Barrel_Jack_CUI_PJ-102AH";1;"BARREL_JACK";;;
14;"D1";"LED_0805_HandSoldering";1;"12v_LED";;;
15;"D2";"LED_0805_HandSoldering";1;"D13_LED";;;
16;"D3";"LED_0805_HandSoldering";1;"D12_LED";;;
17;"D4";"LED_0805_HandSoldering";1;"D11_LED";;;
18;"D5";"LED_0805_HandSoldering";1;"5v_LED";;;
19;"D6";"LED_0805_HandSoldering";1;"USB_LED";;;
20;"D7";"LED_0805_HandSoldering";1;"RX_LED";;;
21;"D8";"LED_0805_HandSoldering";1;"TX_LED";;;
22;"D9,D10,D11,D12";"D_SOD-123F";4;"FlyBack";;;
23;"F1";"R_1812_HandSoldering";1;"Polyfuse";;;
24;"JP1";"SW_SPST_PTS645";1;"Reset SW";;;
25;"JP2";"Slide SW";1;"PWR SW";;;
26;"P1";"USB_Micro-B";1;"USB_OTG";;;
27;"P2,P4,P6,P8,P10,P12";"Socket_Strip_Straight_1x03_Pitch2.54mm";6;"Analog";;;
28;"P3,P5,P7,P9,P11,P13";"Socket_Strip_Straight_1x03_Pitch2.54mm";6;"Digital";;;
29;"Q1";"TO-252-2_Rectifier";1;"Q_PMOS_GDS";;;
30;"Q2,Q3";"LED_D5.0mm-3";2;"IR Receiver";;;
31;"R1";"R_0805_HandSoldering";1;"500";;;
32;"R2,R3,R4,R5,R6";"R_0805_HandSoldering";5;"150";;;
33;"R9";"R_0805_HandSoldering";1;"10K";;;
34;"R10,R11";"R_0805_HandSoldering";2;"330";;;
35;"R17,R18";"R_0805_HandSoldering";2;"10k";;;
36;"U1";"TO-252-2";1;"ZLDO1117K50TC";;;
37;"U3";"PCA9685PW";1;"SOT361-1_2";;;
38;"U4,U5";"SSOP-24_5.3x8.2mm_Pitch0.65mm";2;"TB6612FNG";;;
39;"Y1";"Crystal_SMD_Abracon_ABM3-2pin_5.0x3.2mm_HandSoldering";1;"16MHz";;;
40;"J1,J2";"SL-105-X-XX_1x05";2;"Screw_Terminal_1x05";;;
41;"R7,R8";"R_0603_HandSoldering";2;"22";;;
42;"P14";"SDL-106-X-XX_2x03";1;"CONN_01X06";;;
43;"C23,C24,C25";"C_0603_HandSoldering";3;"C_Small";;;
44;"L1,L2,L3,L4";"R_0805_HandSoldering";4;"Ferrite_Bead_Small";;;

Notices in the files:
projects/omerk_vocore_evk/version_current/working/readme.md:
CC BY-SA 4.0
parts and their libraries:
Copyright 2016 Accelerated Designs. All rights reserved.
